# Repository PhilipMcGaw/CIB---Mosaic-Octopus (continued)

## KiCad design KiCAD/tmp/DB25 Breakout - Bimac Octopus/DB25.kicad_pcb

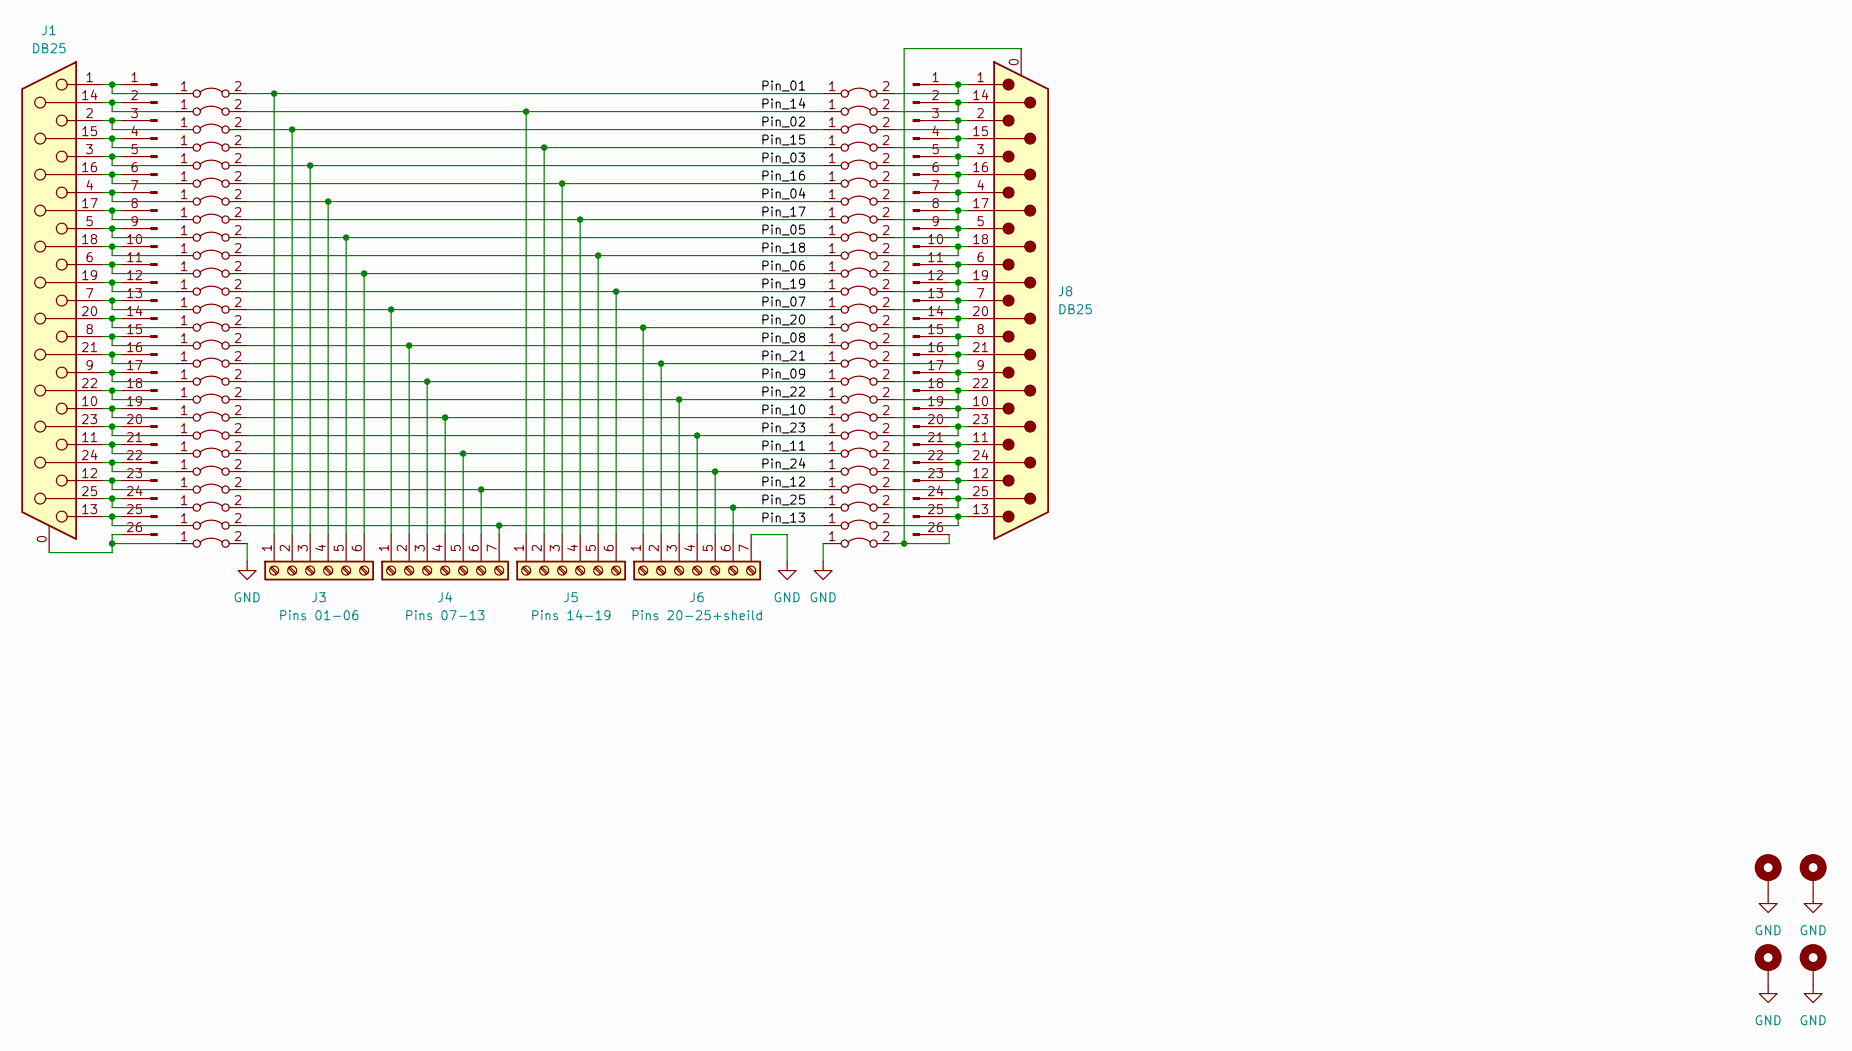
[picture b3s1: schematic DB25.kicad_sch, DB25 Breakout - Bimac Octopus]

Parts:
H1, H2, H3, H4: MountingHole; MountingHole_3.5mm_Pad
J1: DB25; DSUB-25_Female_Horizontal_P2.77x2.84mm_EdgePinOffset7.70mm_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
J2, J7: Pin Header; PinHeader_2x13_P2.54mm_Vertical
J3: Pins 01-06; TerminalBlock_Phoenix_MPT-0,5-6-2.54_1x06_P2.54mm_Horizontal
J4: Pins 07-13; TerminalBlock_Phoenix_MPT-0,5-7-2.54_1x07_P2.54mm_Horizontal
J5: Pins 14-19; TerminalBlock_Phoenix_MPT-0,5-6-2.54_1x06_P2.54mm_Horizontal
J6: Pins 20-25+sheild; TerminalBlock_Phoenix_MPT-0,5-7-2.54_1x07_P2.54mm_Horizontal
J8: DB25; DSUB-25_Male_Horizontal_P2.77x2.84mm_EdgePinOffset7.70mm_Ho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
JP1, JP27: Pin_01; SolderJumper-2_P1.3mm_Bridged_RoundedPad1.0x1.5mm
JP2, JP28: Pin_14; SolderJumper-2_P1.3mm_Bridged_RoundedPad1.0x1.5mm
JP3, JP29: Pin_02; SolderJumper-2_P1.3mm_Bridged_RoundedPad1.0x1.5mm
JP4, JP30: Pin_15; SolderJumper-2_P1.3mm_Bridged_RoundedPad1.0x1.5mm
JP5, JP31: Pin_03; SolderJumper-2_P1.3mm_Bridged_RoundedPad1.0x1.5mm
JP6, JP32: Pin_16; SolderJumper-2_P1.3mm_Bridged_RoundedPad1.0x1.5mm
JP7, JP33: Pin_04; SolderJumper-2_P1.3mm_Bridged_RoundedPad1.0x1.5mm
JP8, JP34: Pin_17; SolderJumper-2_P1.3mm_Bridged_RoundedPad1.0x1.5mm
JP9, JP35: Pin_05; SolderJumper-2_P1.3mm_Bridged_RoundedPad1.0x1.5mm
JP10, JP36: Pin_18; SolderJumper-2_P1.3mm_Bridged_RoundedPad1.0x1.5mm
JP11, JP37: Pin_06; SolderJumper-2_P1.3mm_Bridged_RoundedPad1.0x1.5mm
JP12, JP38: Pin_19; SolderJumper-2_P1.3mm_Bridged_RoundedPad1.0x1.5mm
JP13, JP39: Pin_07; SolderJumper-2_P1.3mm_Bridged_RoundedPad1.0x1.5mm
JP14, JP40: Pin_20; SolderJumper-2_P1.3mm_Bridged_RoundedPad1.0x1.5mm
JP15, JP41: Pin_08; SolderJumper-2_P1.3mm_Bridged_RoundedPad1.0x1.5mm
JP16, JP42: Pin_21; SolderJumper-2_P1.3mm_Bridged_RoundedPad1.0x1.5mm
JP17, JP43: Pin_09; SolderJumper-2_P1.3mm_Bridged_RoundedPad1.0x1.5mm
JP18, JP44: Pin_22; SolderJumper-2_P1.3mm_Bridged_RoundedPad1.0x1.5mm
JP19, JP45: Pin_10; SolderJumper-2_P1.3mm_Bridged_RoundedPad1.0x1.5mm
JP20, JP46: Pin_23; SolderJumper-2_P1.3mm_Bridged_RoundedPad1.0x1.5mm
JP21, JP47: Pin_11; SolderJumper-2_P1.3mm_Bridged_RoundedPad1.0x1.5mm
JP22, JP48: Pin_24; SolderJumper-2_P1.3mm_Bridged_RoundedPad1.0x1.5mm
JP23, JP49: Pin_12; SolderJumper-2_P1.3mm_Bridged_RoundedPad1.0x1.5mm
JP24, JP50: Pin_25; SolderJumper-2_P1.3mm_Bridged_RoundedPad1.0x1.5mm
JP25, JP51: Pin_13; SolderJumper-2_P1.3mm_Bridged_RoundedPad1.0x1.5mm
JP26, JP52: Sheild; SolderJumper-2_P1.3mm_Bridged_RoundedPad1.0x1.5mm

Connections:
/Pin_01: J3.1, JP1.2 (B), JP27.1 (A)
/Pin_02: J3.2, JP3.2 (B), JP29.1 (A)
/Pin_03: J3.3, JP5.2 (B), JP31.1 (A)
/Pin_04: J3.4, JP7.2 (B), JP33.1 (A)
/Pin_05: J3.5, JP9.2 (B), JP35.1 (A)
/Pin_06: J3.6, JP11.2 (B), JP37.1 (A)
/Pin_07: J4.1, JP13.2 (B), JP39.1 (A)
/Pin_08: J4.2, JP15.2 (B), JP41.1 (A)
/Pin_09: J4.3, JP17.2 (B), JP43.1 (A)
/Pin_10: J4.4, JP19.2 (B), JP45.1 (A)
/Pin_11: J4.5, JP21.2 (B), JP47.1 (A)
/Pin_12: J4.6, JP23.2 (B), JP49.1 (A)
/Pin_13: J4.7, JP25.2 (B), JP51.1 (A)
/Pin_14: J5.1, JP2.2 (B), JP28.1 (A)
/Pin_15: J5.2, JP4.2 (B), JP30.1 (A)
/Pin_16: J5.3, JP6.2 (B), JP32.1 (A)
/Pin_17: J5.4, JP8.2 (B), JP34.1 (A)
/Pin_18: J5.5, JP10.2 (B), JP36.1 (A)
/Pin_19: J5.6, JP12.2 (B), JP38.1 (A)
/Pin_20: J6.1, JP14.2 (B), JP40.1 (A)
/Pin_21: J6.2, JP16.2 (B), JP42.1 (A)
/Pin_22: J6.3, JP18.2 (B), JP44.1 (A)
/Pin_23: J6.4, JP20.2 (B), JP46.1 (A)
/Pin_24: J6.5, JP22.2 (B), JP48.1 (A)
/Pin_25: J6.6, JP24.2 (B), JP50.1 (A)
GND: H1.1, H2.1, H3.1, H4.1, J6.7, JP26.2 (B), JP52.1 (A)
unnamed: J1.14, J2.2, JP2.1 (A)
unnamed: J1.15, J2.4, JP4.1 (A)
unnamed: J1.16, J2.6, JP6.1 (A)
unnamed: J1.17, J2.8, JP8.1 (A)
unnamed: J1.18, J2.10, JP10.1 (A)
unnamed: J1.19, J2.12, JP12.1 (A)
unnamed: J1.20, J2.14, JP14.1 (A)
unnamed: J1.21, J2.16, JP16.1 (A)
unnamed: J1.22, J2.18, JP18.1 (A)
unnamed: J1.23, J2.20, JP20.1 (A)
unnamed: J1.24, J2.22, JP22.1 (A)
unnamed: J1.25, J2.24, JP24.1 (A)
unnamed: J1.0 (PAD), J2.26, JP26.1 (A)
unnamed: J1.1, J2.1, JP1.1 (A)
unnamed: J1.2, J2.3, JP3.1 (A)
unnamed: J1.3, J2.5, JP5.1 (A)
unnamed: J1.4, J2.7, JP7.1 (A)
unnamed: J1.5, J2.9, JP9.1 (A)
unnamed: J1.6, J2.11, JP11.1 (A)
unnamed: J1.7, J2.13, JP13.1 (A)
unnamed: J1.8, J2.15, JP15.1 (A)
unnamed: J1.9, J2.17, JP17.1 (A)
unnamed: J1.10, J2.19, JP19.1 (A)
unnamed: J1.11, J2.21, JP21.1 (A)
unnamed: J1.12, J2.23, JP23.1 (A)
unnamed: J1.13, J2.25, JP25.1 (A)
unnamed: J7.1, J8.1, JP27.2 (B)
unnamed: J7.2, J8.14, JP28.2 (B)
unnamed: J7.3, J8.2, JP29.2 (B)
unnamed: J7.4, J8.15, JP30.2 (B)
unnamed: J7.5, J8.3, JP31.2 (B)
unnamed: J7.6, J8.16, JP32.2 (B)
unnamed: J7.7, J8.4, JP33.2 (B)
unnamed: J7.8, J8.17, JP34.2 (B)
unnamed: J7.9, J8.5, JP35.2 (B)
unnamed: J7.10, J8.18, JP36.2 (B)
unnamed: J7.11, J8.6, JP37.2 (B)
unnamed: J7.12, J8.19, JP38.2 (B)
unnamed: J7.13, J8.7, JP39.2 (B)
unnamed: J7.14, J8.20, JP40.2 (B)
unnamed: J7.15, J8.8, JP41.2 (B)
unnamed: J7.16, J8.21, JP42.2 (B)
unnamed: J7.17, J8.9, JP43.2 (B)
unnamed: J7.18, J8.22, JP44.2 (B)
unnamed: J7.19, J8.10, JP45.2 (B)
unnamed: J7.20, J8.23, JP46.2 (B)
unnamed: J7.21, J8.11, JP47.2 (B)
unnamed: J7.22, J8.24, JP48.2 (B)
unnamed: J7.23, J8.12, JP49.2 (B)
unnamed: J7.24, J8.25, JP50.2 (B)
unnamed: J7.25, J8.13, JP51.2 (B)
unnamed: J7.26, J8.0 (PAD), JP52.2 (B)

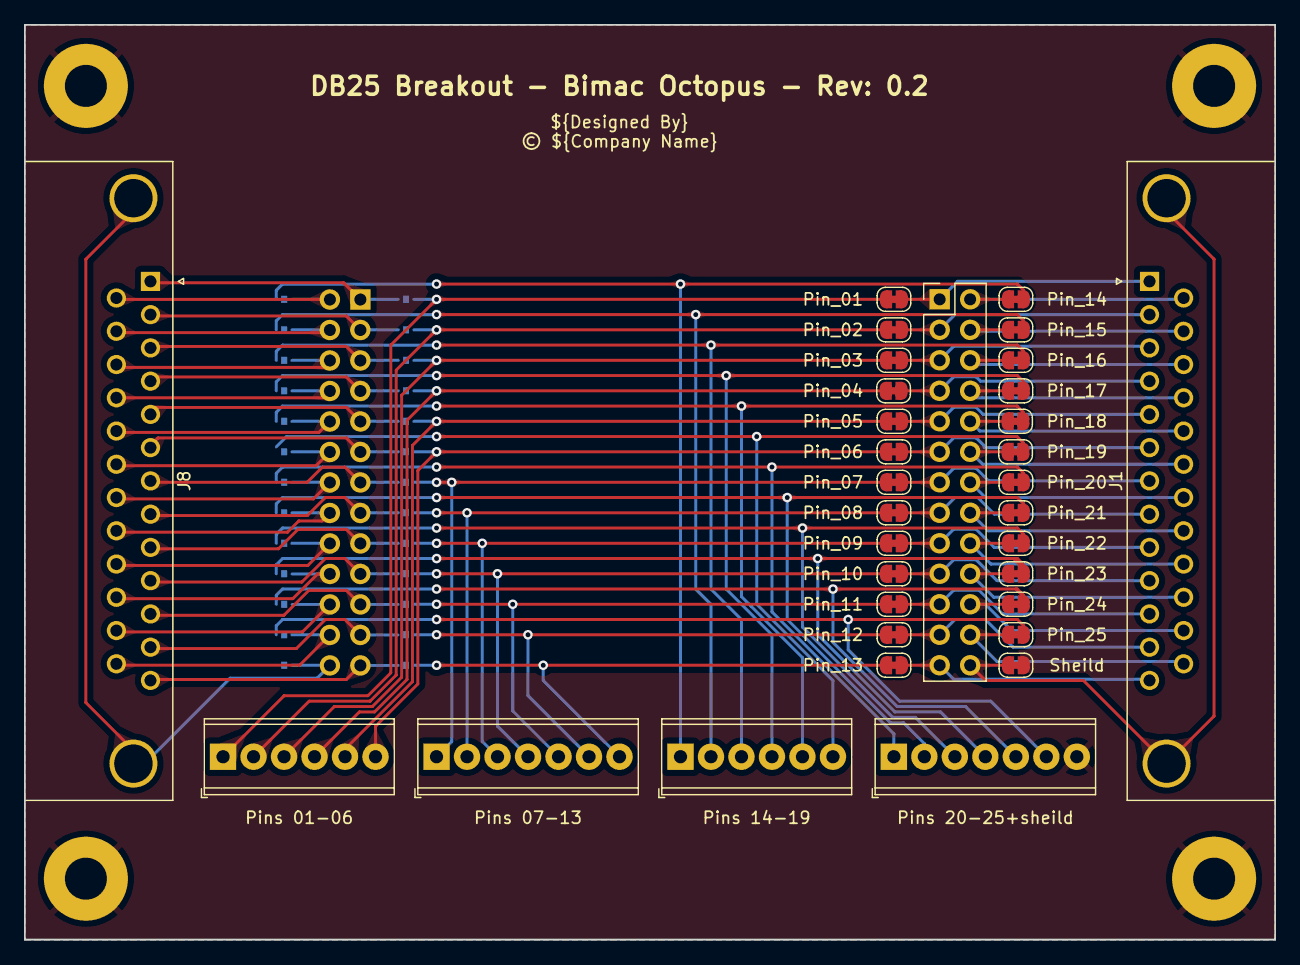
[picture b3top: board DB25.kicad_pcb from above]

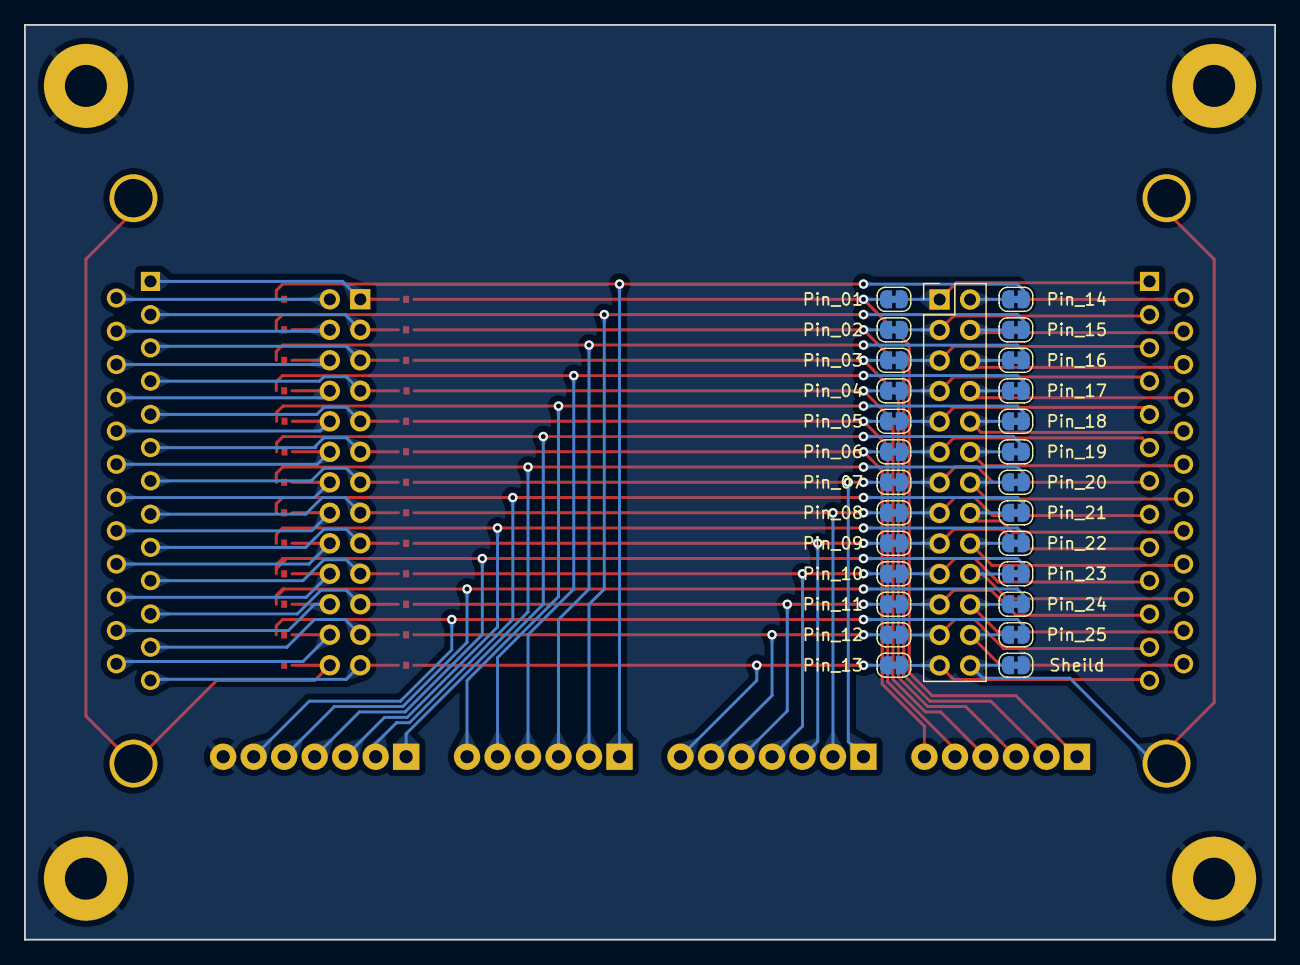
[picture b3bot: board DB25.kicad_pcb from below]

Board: 2 copper layers, 104.1 x 76.2 mm, 64 parts (27 on the bottom side), 78 nets.

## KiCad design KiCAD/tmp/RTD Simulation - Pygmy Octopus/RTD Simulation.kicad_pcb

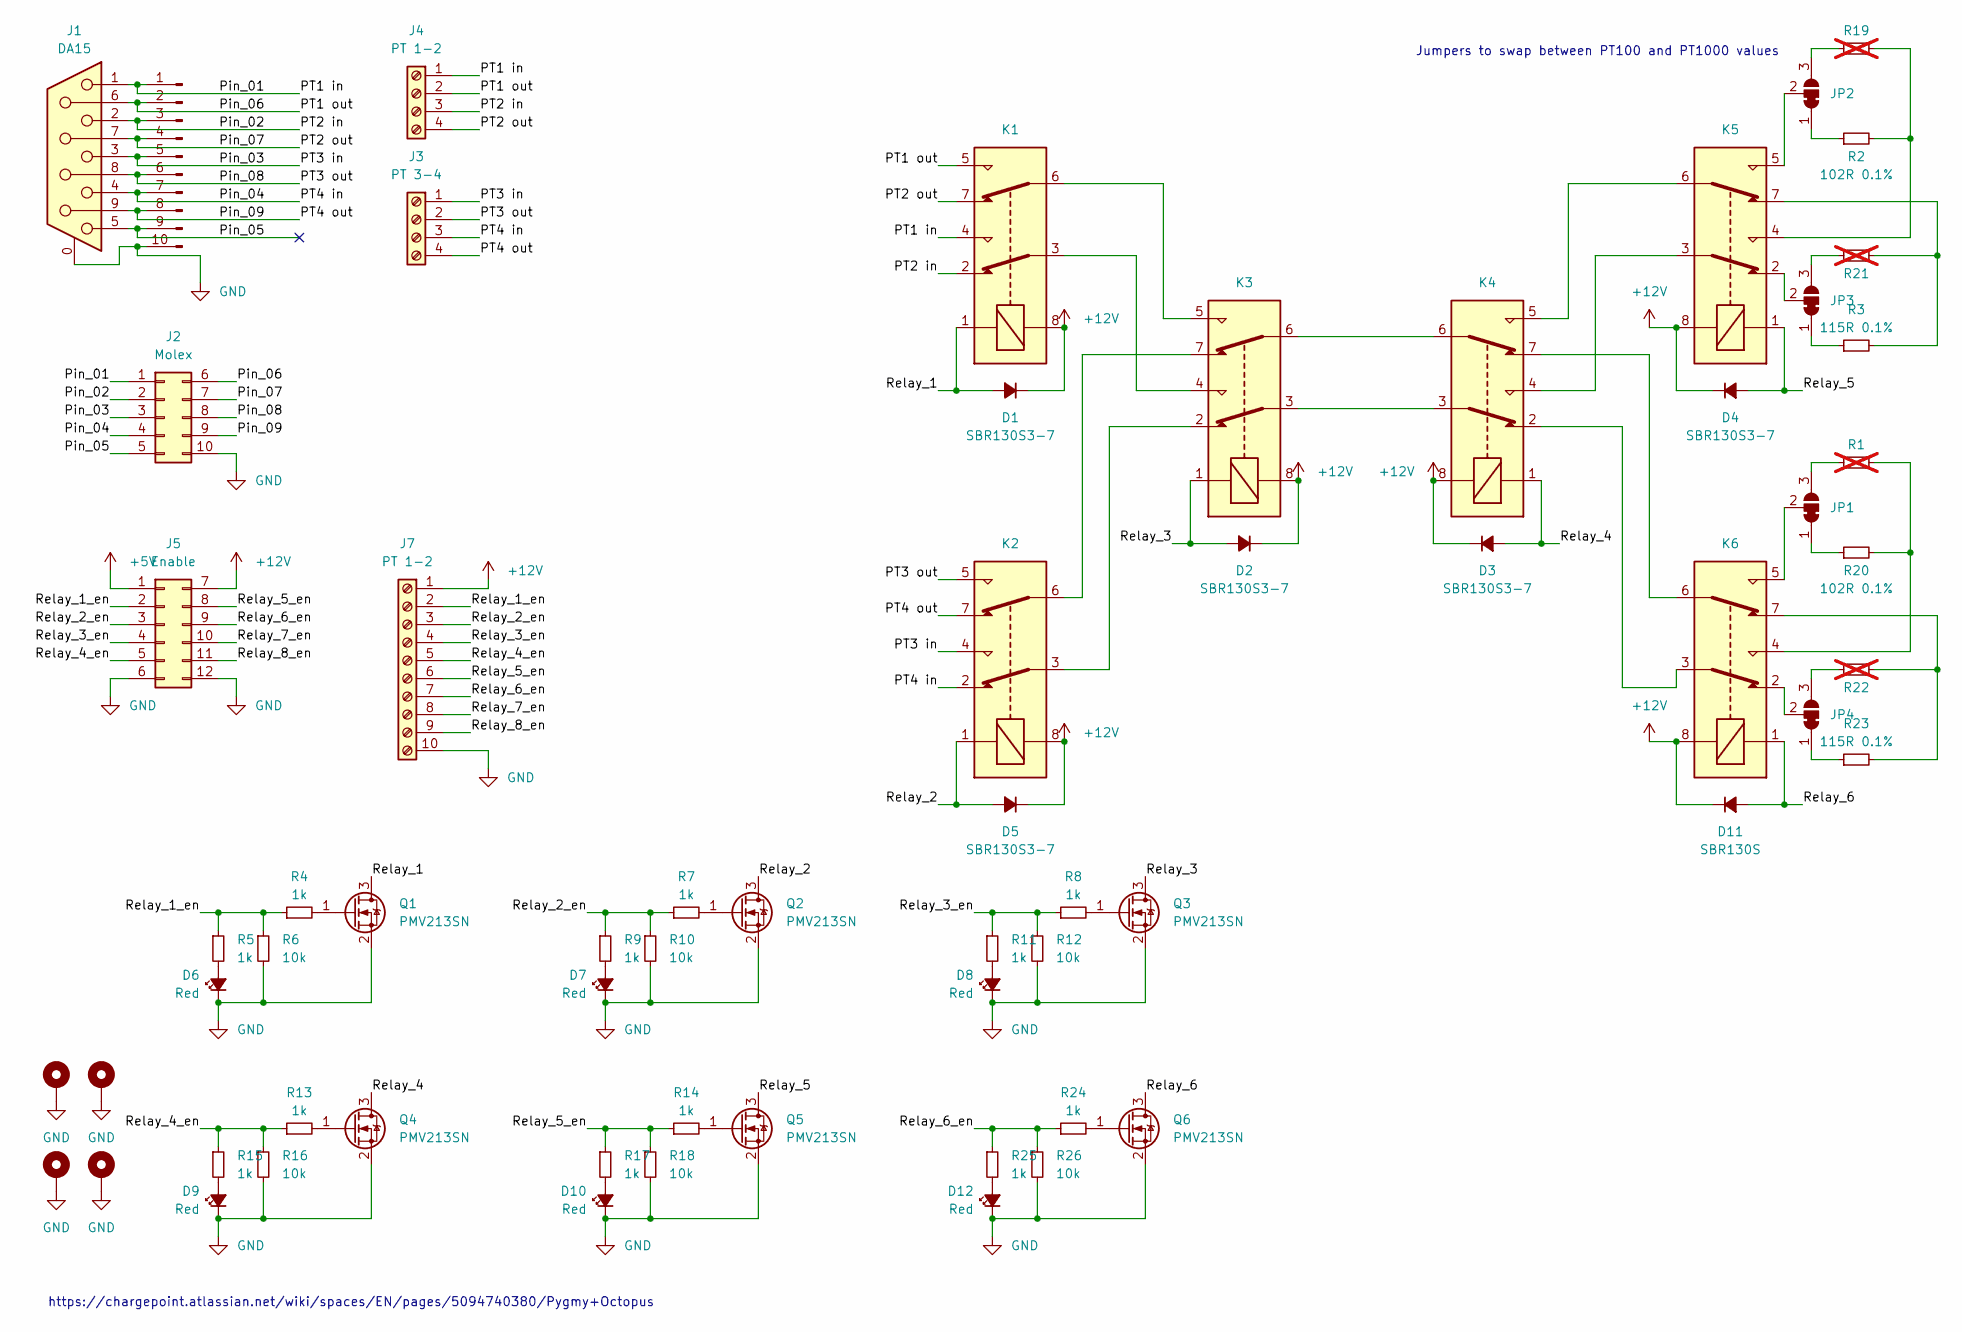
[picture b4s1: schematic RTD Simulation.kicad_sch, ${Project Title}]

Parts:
D1, D2, D3, D4, D5: SBR130S3-7; D_SOD-323_HandSoldering
D6, D7, D8, D9, D10, D12: Red; LED_0805_2012Metric_Pad1.15x1.40mm_HandSolder
D11: SBR130S; D_SOD-323_HandSoldering
H1, H2, H3, H4: MountingHole; MountingHole_3.5mm_Pad
J1: DA15; DSUB-9_Female_Horizontal_P2.77x2.84mm_EdgePinOffset7.70mm_H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
J2: Molex; Molex_Micro-Fit_3.0_43045-1018_2x05-1MP_P3.00mm_Vertical; Farnell FN# 2781942
J3: PT 3-4; TerminalBlock_Phoenix_MPT-0,5-4-2.54_1x04_P2.54mm_Horizontal
J4: PT 1-2; TerminalBlock_Phoenix_MPT-0,5-4-2.54_1x04_P2.54mm_Horizontal
J5: Enable; Molex_Micro-Fit_3.0_43045-1218_2x06-1MP_P3.00mm_Vertical; Farnell FN# 2781942
J6: Pin Header; PinHeader_2x05_P2.54mm_Vertical
J7: PT 1-2; TerminalBlock_Phoenix_MPT-0,5-10-2.54_1x10_P2.54mm_Horizont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
JP1, JP2, JP3, JP4: SolderJumper-3_P1.3mm_Bridged12_Pad1.0x1.5mm
K1, K2, K3, K4, K5, K6: Relay_DPDT_Omron_G6K-2P; Manufacturer # G6K-2P DC12; DigiKey # Z117-ND
Q1, Q2, Q3, Q4, Q5, Q6: PMV213SN; SOT-23
R1, R19, R21, R22: R_1206_3216Metric_Pad1.30x1.75mm_HandSolder; Manufacturer # ERA-8AEB1020V; DigiKey # P102BCCT-ND; not fitted
R2, R20: 102R 0.1%; R_1206_3216Metric_Pad1.30x1.75mm_HandSolder; Manufacturer # ERA-8AEB1020V; DigiKey # P102BCCT-ND
R3, R23: 115R 0.1%; R_1206_3216Metric_Pad1.30x1.75mm_HandSolder; Manufacturer # ERA-8AEB1150V; DigiKey # P115BCCT-ND
R4, R5, R7, R8, R9, R11, R13, R14, R15, R17, R24, R25: 1k; R_0805_2012Metric_Pad1.20x1.40mm_HandSolder
R6, R10, R12, R16, R18, R26: 10k; R_0805_2012Metric_Pad1.20x1.40mm_HandSolder

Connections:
+5V: J5.1
+12V: D1.1 (K), D2.1 (K), D3.1 (K), D4.1 (K), D5.1 (K), D11.1 (K), J5.7, J7.1, K1.8, K2.8, K3.8, K4.8, K5.8, K6.8
/PT1 in: J1.1, J2.1, J4.1, J6.1, K1.4
/PT1 out: J1.6, J2.6, J4.2, J6.2, K1.5
/PT2 in: J1.2, J2.2, J4.3, J6.3, K1.2
/PT2 out: J1.7, J2.7, J4.4, J6.4, K1.7
/PT3 in: J1.3, J2.3, J3.1, J6.5, K2.4
/PT3 out: J1.8, J2.8, J3.2, J6.6, K2.5
/PT4 in: J1.4, J2.4, J3.3, J6.7, K2.2
/PT4 out: J1.9, J2.9, J3.4, J6.8, K2.7
/Pin_05: J1.5, J2.5, J6.9
/Relay_1: D1.2 (A), K1.1, Q1.3 (D)
/Relay_1_en: J5.2, J7.2, R4.1, R5.1, R6.1
/Relay_2: D5.2 (A), K2.1, Q2.3 (D)
/Relay_2_en: J5.3, J7.3, R7.1, R9.1, R10.1
/Relay_3: D2.2 (A), K3.1, Q3.3 (D)
/Relay_3_en: J5.4, J7.4, R8.1, R11.1, R12.1
/Relay_4: D3.2 (A), K4.1, Q4.3 (D)
/Relay_4_en: J5.5, J7.5, R13.1, R15.1, R16.1
/Relay_5: D4.2 (A), K5.1, Q5.3 (D)
/Relay_5_en: J5.8, J7.6, R14.1, R17.1, R18.1
/Relay_6: D11.2 (A), K6.1, Q6.3 (D)
/Relay_6_en: J5.9, J7.7, R24.1, R25.1, R26.1
/Relay_7_en: J5.10, J7.8
/Relay_8_en: J5.11, J7.9
GND: D6.1 (K), D7.1 (K), D8.1 (K), D9.1 (K), D10.1 (K), D12.1 (K), H1.1, H2.1, H3.1, H4.1, J1.0 (PAD), J2.10, J5.6, J5.12, J6.10, J7.10, Q1.2 (S), Q2.2 (S), Q3.2 (S), Q4.2 (S), Q5.2 (S), Q6.2 (S), R6.2, R10.2, R12.2, R16.2, R18.2, R26.2
unnamed: D6.2 (A), R5.2
unnamed: D7.2 (A), R9.2
unnamed: D8.2 (A), R11.2
unnamed: D9.2 (A), R15.2
unnamed: D10.2 (A), R17.2
unnamed: D12.2 (A), R25.2
unnamed: JP1.1 (A), R20.1
unnamed: JP1.3 (B), R1.1
unnamed: JP1.2 (C), K6.5
unnamed: JP2.1 (A), R2.1
unnamed: JP2.3 (B), R19.1
unnamed: JP2.2 (C), K5.5
unnamed: JP3.1 (A), R3.1
unnamed: JP3.3 (B), R21.1
unnamed: JP3.2 (C), K5.2
unnamed: JP4.1 (A), R23.1
unnamed: JP4.3 (B), R22.1
unnamed: JP4.2 (C), K6.2
unnamed: K1.3, K3.4
unnamed: K1.6, K3.5
unnamed: K2.3, K3.2
unnamed: K2.6, K3.7
unnamed: K3.3, K4.3
unnamed: K3.6, K4.6
unnamed: K4.2, K6.3
unnamed: K4.4, K5.3
unnamed: K4.5, K5.6
unnamed: K4.7, K6.6
unnamed: K5.4, R2.2, R19.2
unnamed: K5.7, R3.2, R21.2
unnamed: K6.4, R1.2, R20.2
unnamed: K6.7, R22.2, R23.2
unnamed: Q1.1 (G), R4.2
unnamed: Q2.1 (G), R7.2
unnamed: Q3.1 (G), R8.2
unnamed: Q4.1 (G), R13.2
unnamed: Q5.1 (G), R14.2
unnamed: Q6.1 (G), R24.2

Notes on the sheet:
https://chargepoint.atlassian.net/wiki/spaces/EN/pages/5094740380/Pygmy+Octopus
Jumpers to swap between PT100 and PT1000 values

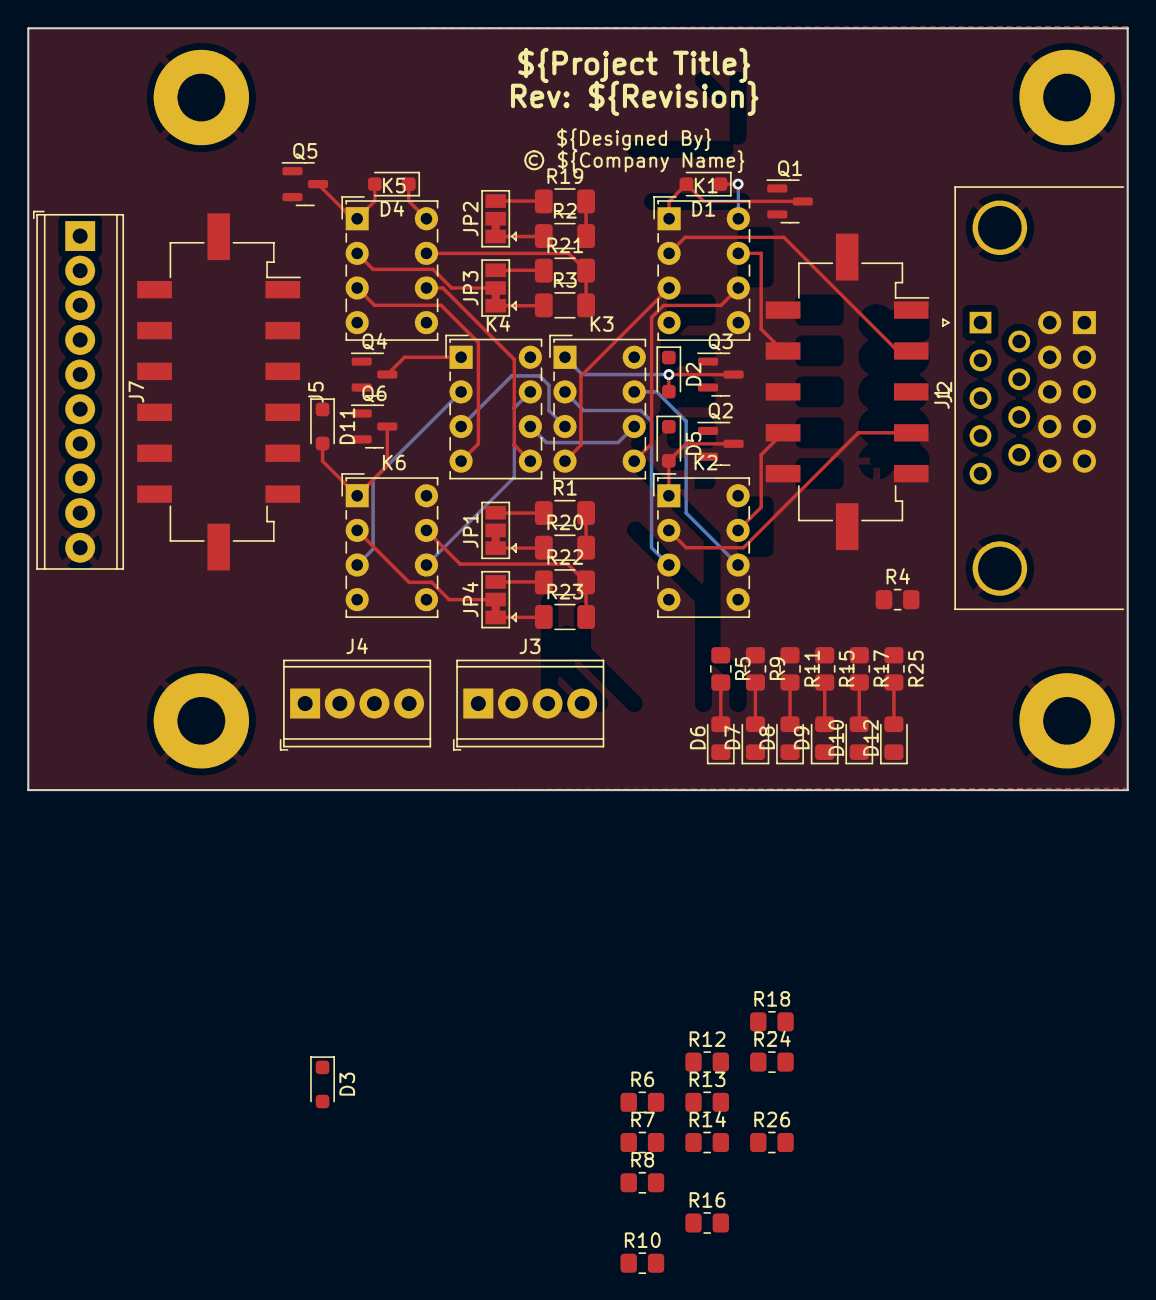
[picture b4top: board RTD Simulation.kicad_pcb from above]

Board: 2 copper layers, 80.6 x 55.9 mm, 65 parts (1 on the bottom side), 63 nets.

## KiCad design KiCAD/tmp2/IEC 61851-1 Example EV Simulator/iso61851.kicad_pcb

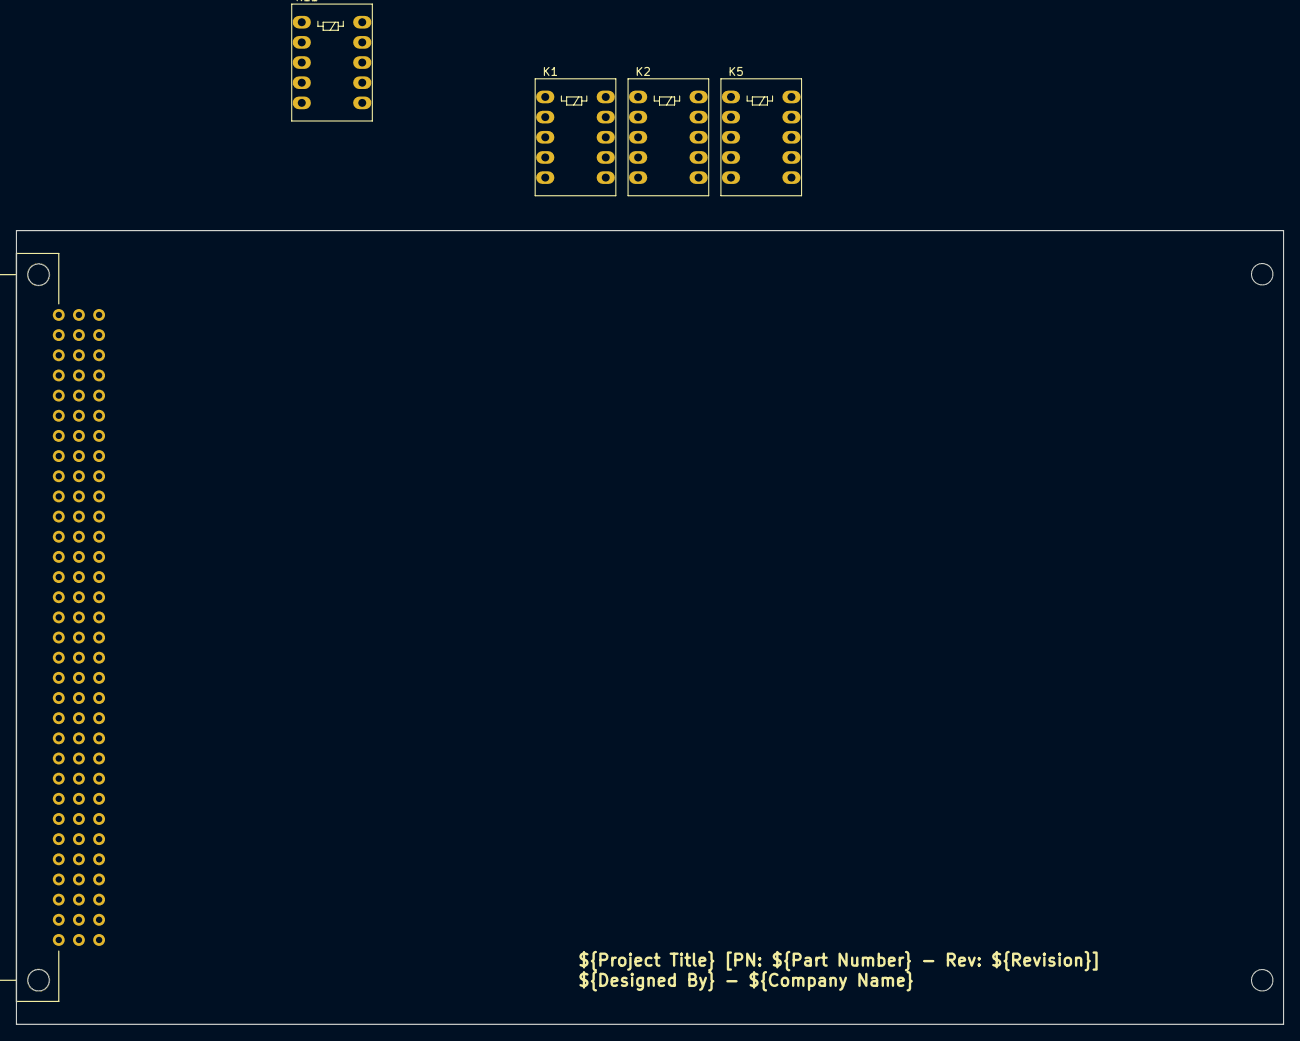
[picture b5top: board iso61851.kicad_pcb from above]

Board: 2 copper layers, 159.6 x 100.0 mm, 5 parts (0 on the bottom side), 4 nets, no tracks yet.

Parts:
J1: 03x32_DIN41612; Eurocard
K1: SW-Pr_a; Relay_DPDT_FRT5
K2: SW-Pr_b; Relay_DPDT_FRT5
K5: SW-Cc; Relay_DPDT_FRT5
K11: SW-Sh; Relay_DPDT_FRT5

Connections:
+5V0: J1.4a (Pin_4), J1.4b (Pin_4)
+12V: J1.5a (Pin_5), J1.5b (Pin_5), J1.5c (Pin_5)
GND: J1.3a (Pin_3), J1.3b (Pin_3), J1.6a (Pin_6), J1.6b (Pin_6), J1.6c (Pin_6), J1.15a (Pin_15), J1.15b (Pin_15), J1.15c (Pin_15)
unnamed: K1.7, K2.8

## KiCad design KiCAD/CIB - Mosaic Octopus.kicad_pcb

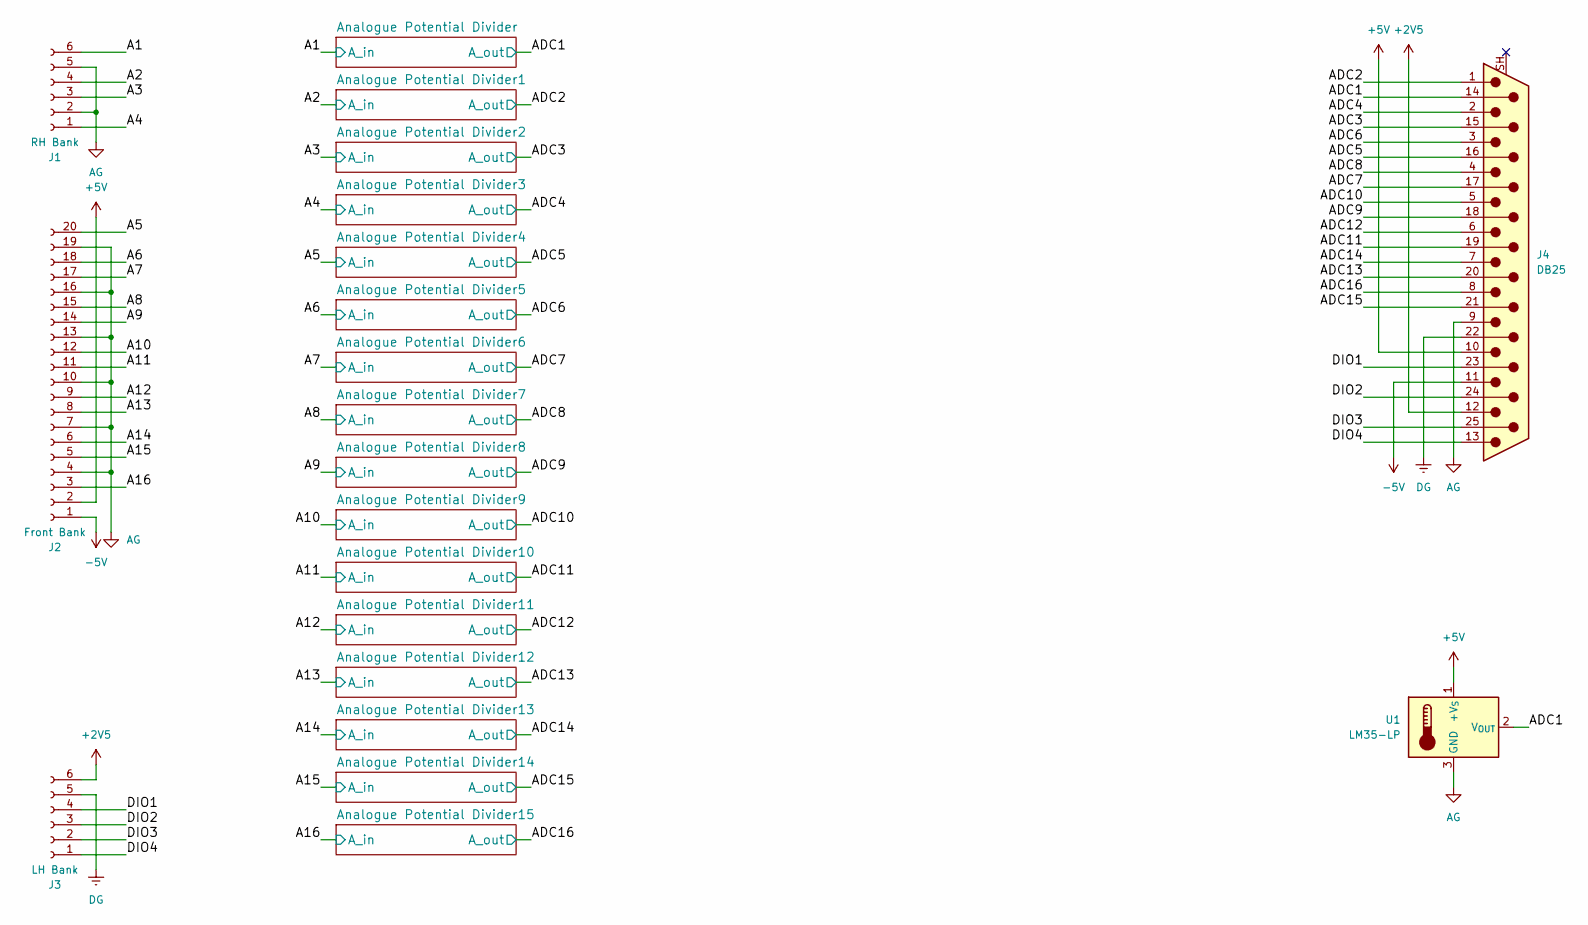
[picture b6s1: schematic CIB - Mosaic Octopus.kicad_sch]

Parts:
J1: RH Bank; TerminalBlock_CUI_TB007-508-06_1x06_P5.08mm_Horizontal
J2: Front Bank; TerminalBlock_CUI_TB007-508-20_1x20_P5.08mm_Horizontal
J3: LH Bank; TerminalBlock_CUI_TB007-508-06_1x06_P5.08mm_Horizontal
J4: DB25; DSUB-25_Pins_Horizontal_P2.77x2.84mm_EdgePinOffset4.94mm_Ho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
U1: LM35-LP; TO-92_Inline

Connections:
+2V5: J3.6, J4.12
+5V: J2.2, J4.10, U1.1 (+V_{S}); also elsewhere on the board
-5V: J2.1, J4.11; also elsewhere on the board
/A1: J1.6; also elsewhere on the board
/A2: J1.4; also elsewhere on the board
/A3: J1.3; also elsewhere on the board
/A4: J1.1; also elsewhere on the board
/A5: J2.20; also elsewhere on the board
/A6: J2.18; also elsewhere on the board
/A7: J2.17; also elsewhere on the board
/A8: J2.15; also elsewhere on the board
/A9: J2.14; also elsewhere on the board
/A10: J2.12; also elsewhere on the board
/A11: J2.11; also elsewhere on the board
/A12: J2.9; also elsewhere on the board
/A13: J2.8; also elsewhere on the board
/A14: J2.6; also elsewhere on the board
/A15: J2.5; also elsewhere on the board
/A16: J2.3; also elsewhere on the board
/ADC1: J4.14, U1.2 (V_{OUT}); also elsewhere on the board
/ADC2: J4.1; also elsewhere on the board
/ADC3: J4.15; also elsewhere on the board
/ADC4: J4.2; also elsewhere on the board
/ADC5: J4.16; also elsewhere on the board
/ADC6: J4.3; also elsewhere on the board
/ADC7: J4.17; also elsewhere on the board
/ADC8: J4.4; also elsewhere on the board
/ADC9: J4.18; also elsewhere on the board
/ADC10: J4.5; also elsewhere on the board
/ADC11: J4.19; also elsewhere on the board
/ADC12: J4.6; also elsewhere on the board
/ADC13: J4.20; also elsewhere on the board
/ADC14: J4.7; also elsewhere on the board
/ADC15: J4.21; also elsewhere on the board
/ADC16: J4.8; also elsewhere on the board
/DIO1: J3.4, J4.23
/DIO2: J3.3, J4.24
/DIO3: J3.2, J4.25
/DIO4: J3.1, J4.13
AG: J1.2, J1.5, J2.4, J2.7, J2.10, J2.13, J2.16, J2.19, J4.9, U1.3 (GND); also elsewhere on the board
DG: J3.5, J4.22

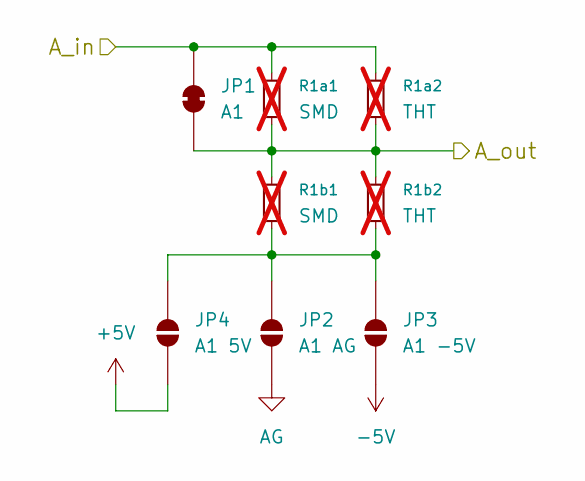
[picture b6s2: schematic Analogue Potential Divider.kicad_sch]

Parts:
JP1: A1; SolderJumper-2_P1.3mm_Bridged_RoundedPad1.0x1.5mm
JP2: A1 AG; SolderJumper-2_P1.3mm_Open_RoundedPad1.0x1.5mm
JP3: A1 -5V; SolderJumper-2_P1.3mm_Open_RoundedPad1.0x1.5mm
JP4: A1 5V; SolderJumper-2_P1.3mm_Open_RoundedPad1.0x1.5mm
R1a1, R1b1: SMD; R_0805_2012Metric_Pad1.20x1.40mm_HandSolder; not fitted
R1a2, R1b2: THT; R_Axial_DIN0207_L6.3mm_D2.5mm_P10.16mm_Horizontal; not fitted

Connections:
+5V: JP4.1 (A); also elsewhere on the board
-5V: JP3.1 (A); also elsewhere on the board
/A1: JP1.2 (B), R1a1.1, R1a2.1; also elsewhere on the board
/ADC1: JP1.1 (A), R1a1.2, R1a2.2, R1b1.1, R1b2.1; also elsewhere on the board
AG: JP2.1 (A); also elsewhere on the board
unnamed: JP2.2 (B), JP3.2 (B), JP4.2 (B), R1b1.2, R1b2.2

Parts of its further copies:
JP5, JP9, JP13, JP17, JP21, JP25, JP29, JP33, JP37, JP41, JP45, JP49, JP53, JP57, JP61: A1 5V; SolderJumper-2_P1.3mm_Open_RoundedPad1.0x1.5mm
JP6, JP10, JP14, JP18, JP22, JP26, JP30, JP34, JP38, JP42, JP46, JP50, JP54, JP58, JP62: A1; SolderJumper-2_P1.3mm_Bridged_RoundedPad1.0x1.5mm
JP7, JP11, JP15, JP19, JP23, JP27, JP31, JP35, JP39, JP43, JP47, JP51, JP55, JP59, JP63: A1 AG; SolderJumper-2_P1.3mm_Open_RoundedPad1.0x1.5mm
JP8, JP12, JP16, JP20, JP24, JP28, JP32, JP36, JP40, JP44, JP48, JP52, JP56, JP60, JP64: A1 -5V; SolderJumper-2_P1.3mm_Open_RoundedPad1.0x1.5mm
R1a3, R1a5, R1a7, R1a9, R1a11, R1a13, R1a15, R1a17, R1a19, R1a21, R1a23, R1a25, R1a27, R1a29, R1a31, R1b3, R1b5, R1b7, R1b9, R1b11, R1b13, R1b15, R1b17, R1b19, R1b21, R1b23, R1b25, R1b27, R1b29, R1b31: SMD; R_0805_2012Metric_Pad1.20x1.40mm_HandSolder; not fitted
R1a4, R1a6, R1a8, R1a10, R1a12, R1a14, R1a16, R1a18, R1a20, R1a22, R1a24, R1a26, R1a28, R1a30, R1a32, R1b4, R1b6, R1b8, R1b10, R1b12, R1b14, R1b16, R1b18, R1b20, R1b22, R1b24, R1b26, R1b28, R1b30, R1b32: THT; R_Axial_DIN0207_L6.3mm_D2.5mm_P10.16mm_Horizontal; not fitted

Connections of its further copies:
+5V: JP5.1 (A), JP9.1 (A), JP13.1 (A), JP17.1 (A), JP21.1 (A), JP25.1 (A), JP29.1 (A), JP33.1 (A), JP37.1 (A), JP41.1 (A), JP45.1 (A), JP49.1 (A), JP53.1 (A), JP57.1 (A), JP61.1 (A); also elsewhere on the board
-5V: JP8.1 (A), JP12.1 (A), JP16.1 (A), JP20.1 (A), JP24.1 (A), JP28.1 (A), JP32.1 (A), JP36.1 (A), JP40.1 (A), JP44.1 (A), JP48.1 (A), JP52.1 (A), JP56.1 (A), JP60.1 (A), JP64.1 (A); also elsewhere on the board
/A2: JP6.2 (B), R1a3.1, R1a4.1; also elsewhere on the board
/A3: JP10.2 (B), R1a5.1, R1a6.1; also elsewhere on the board
/A4: JP14.2 (B), R1a7.1, R1a8.1; also elsewhere on the board
/A5: JP18.2 (B), R1a9.1, R1a10.1; also elsewhere on the board
/A6: JP22.2 (B), R1a11.1, R1a12.1; also elsewhere on the board
/A7: JP26.2 (B), R1a13.1, R1a14.1; also elsewhere on the board
/A8: JP30.2 (B), R1a15.1, R1a16.1; also elsewhere on the board
/A9: JP34.2 (B), R1a17.1, R1a18.1; also elsewhere on the board
/A10: JP38.2 (B), R1a19.1, R1a20.1; also elsewhere on the board
/A11: JP42.2 (B), R1a21.1, R1a22.1; also elsewhere on the board
/A12: JP46.2 (B), R1a23.1, R1a24.1; also elsewhere on the board
/A13: JP50.2 (B), R1a25.1, R1a26.1; also elsewhere on the board
/A14: JP54.2 (B), R1a27.1, R1a28.1; also elsewhere on the board
/A15: JP58.2 (B), R1a29.1, R1a30.1; also elsewhere on the board
/A16: JP62.2 (B), R1a31.1, R1a32.1; also elsewhere on the board
/ADC2: JP6.1 (A), R1a3.2, R1a4.2, R1b3.1, R1b4.1; also elsewhere on the board
/ADC3: JP10.1 (A), R1a5.2, R1a6.2, R1b5.1, R1b6.1; also elsewhere on the board
/ADC4: JP14.1 (A), R1a7.2, R1a8.2, R1b7.1, R1b8.1; also elsewhere on the board
/ADC5: JP18.1 (A), R1a9.2, R1a10.2, R1b9.1, R1b10.1; also elsewhere on the board
/ADC6: JP22.1 (A), R1a11.2, R1a12.2, R1b11.1, R1b12.1; also elsewhere on the board
/ADC7: JP26.1 (A), R1a13.2, R1a14.2, R1b13.1, R1b14.1; also elsewhere on the board
/ADC8: JP30.1 (A), R1a15.2, R1a16.2, R1b15.1, R1b16.1; also elsewhere on the board
/ADC9: JP34.1 (A), R1a17.2, R1a18.2, R1b17.1, R1b18.1; also elsewhere on the board
/ADC10: JP38.1 (A), R1a19.2, R1a20.2, R1b19.1, R1b20.1; also elsewhere on the board
/ADC11: JP42.1 (A), R1a21.2, R1a22.2, R1b21.1, R1b22.1; also elsewhere on the board
/ADC12: JP46.1 (A), R1a23.2, R1a24.2, R1b23.1, R1b24.1; also elsewhere on the board
/ADC13: JP50.1 (A), R1a25.2, R1a26.2, R1b25.1, R1b26.1; also elsewhere on the board
/ADC14: JP54.1 (A), R1a27.2, R1a28.2, R1b27.1, R1b28.1; also elsewhere on the board
/ADC15: JP58.1 (A), R1a29.2, R1a30.2, R1b29.1, R1b30.1; also elsewhere on the board
/ADC16: JP62.1 (A), R1a31.2, R1a32.2, R1b31.1, R1b32.1; also elsewhere on the board
AG: JP7.1 (A), JP11.1 (A), JP15.1 (A), JP19.1 (A), JP23.1 (A), JP27.1 (A), JP31.1 (A), JP35.1 (A), JP39.1 (A), JP43.1 (A), JP47.1 (A), JP51.1 (A), JP55.1 (A), JP59.1 (A), JP63.1 (A); also elsewhere on the board
unnamed: JP5.2 (B), JP7.2 (B), JP8.2 (B), R1b3.2, R1b4.2
unnamed: JP9.2 (B), JP11.2 (B), JP12.2 (B), R1b5.2, R1b6.2
unnamed: JP13.2 (B), JP15.2 (B), JP16.2 (B), R1b7.2, R1b8.2
unnamed: JP17.2 (B), JP19.2 (B), JP20.2 (B), R1b9.2, R1b10.2
unnamed: JP21.2 (B), JP23.2 (B), JP24.2 (B), R1b11.2, R1b12.2
unnamed: JP25.2 (B), JP27.2 (B), JP28.2 (B), R1b13.2, R1b14.2
unnamed: JP29.2 (B), JP31.2 (B), JP32.2 (B), R1b15.2, R1b16.2
unnamed: JP33.2 (B), JP35.2 (B), JP36.2 (B), R1b17.2, R1b18.2
unnamed: JP37.2 (B), JP39.2 (B), JP40.2 (B), R1b19.2, R1b20.2
unnamed: JP41.2 (B), JP43.2 (B), JP44.2 (B), R1b21.2, R1b22.2
unnamed: JP45.2 (B), JP47.2 (B), JP48.2 (B), R1b23.2, R1b24.2
unnamed: JP49.2 (B), JP51.2 (B), JP52.2 (B), R1b25.2, R1b26.2
unnamed: JP53.2 (B), JP55.2 (B), JP56.2 (B), R1b27.2, R1b28.2
unnamed: JP57.2 (B), JP59.2 (B), JP60.2 (B), R1b29.2, R1b30.2
unnamed: JP61.2 (B), JP63.2 (B), JP64.2 (B), R1b31.2, R1b32.2
